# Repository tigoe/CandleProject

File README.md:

# Candle Project	

This is my candle project. We shall see how it develops.

Tom Igoe <br>
26 June 2015

## Theory of Operation

ESP8266 modules handle the network traffic, and communicate serially to the ATTiny85, which controls the WS2812s. When the candle turns on, it turns two pixels to warm fading, and a thirs to blue. Then the ESP8266 attempts to contact the server. When it succeeds, the third pixel is turned to warm fading.

The metal can of the candle forms a capacitive touch sensor. When a touch is detected, the candle flares the pixels to white, and sends a signal to the server. The server then sends the same message to all the candles, causing them all to flare white. They gradually fade back to the warm glow.

## Communication Protocol

All communications are over UDP. When a new client connects, the server sends "Hello!!!" to the client. When any candle sends a message to the server, the server echoes it to all servers that it's seen since launch.

When a candle receives a * message, it flares white. Similarly, when it receives a touch, it sends a * message.

* Programming

The ATTinys must be removed and programmed with a hardware programmer. The ESP modules can be programmed over the serial connection. The ground of the serial connection is the pin closest to the outside edge of the board. You need to press the IO0 button then the reset on the ESP8266 to put it in programming mode. The  indicator light will grow a dim red when you are in programming mode.

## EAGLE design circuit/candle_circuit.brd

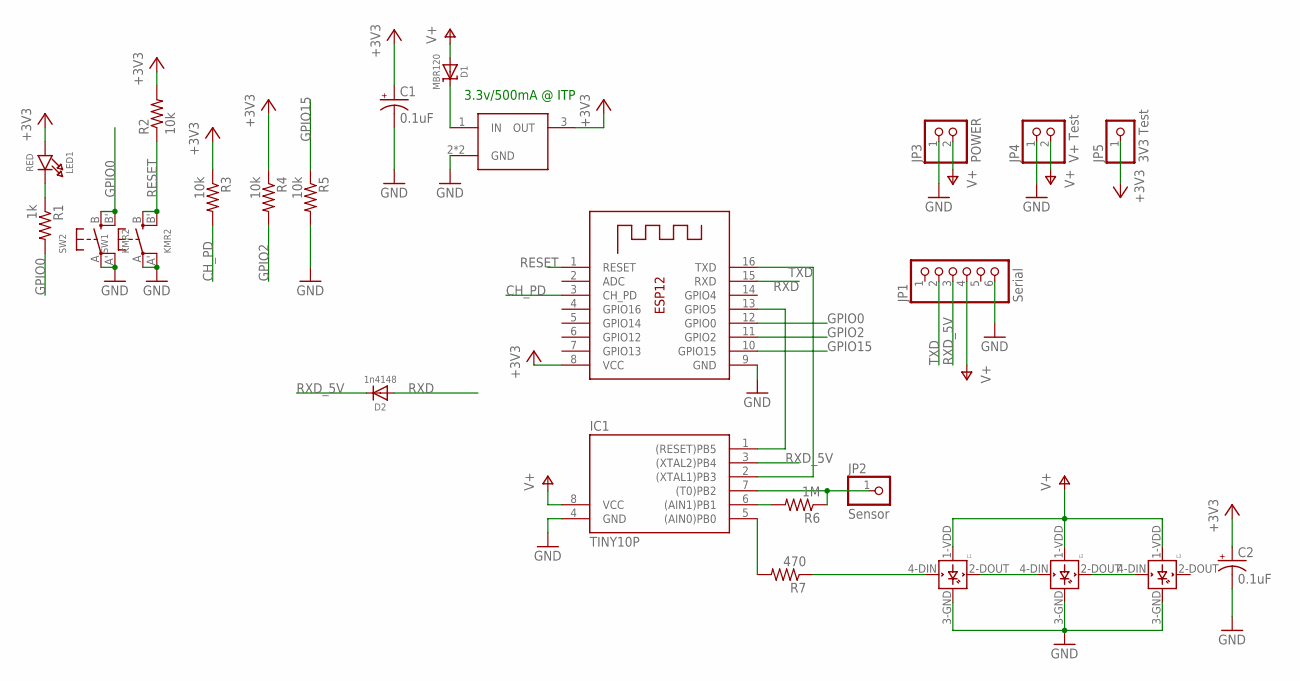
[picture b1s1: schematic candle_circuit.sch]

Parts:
C1, C2: 0.1uF; PANASONIC_C
D1: MBR120; SOD-123
D2: 1n4148; SOD-323
IC1: TINY10P; DIL08
IC2: ESP-12
JP1: Serial; 1X06_OVAL
JP2: Sensor; 1X01
JP3: POWER; 1X02_OVAL
JP4: V+ Test; 1X02_OVAL
JP5: 3V3 Test; 1X01
L1, L2, L3: WS2812B
LED1: RED; CHIPLED_0805_NOOUTLINE
R1: 1k; R0603
R2, R3, R4, R5: 10k; R0603
R6: 1M; R0603
R7: 470; R0603
SW1, SW2: KMR2; BTN_KMR2_4.6X2.8
U1: REGULATOR3.3V-UA78M33CDCYR; SOT223

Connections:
+3V3: C1.+, C2.+, IC2.8 (VCC), JP5.1, LED1.A, R2.2, R3.1, R4.1, U1.3 (OUT)
CH_PD: IC2.3 (CH_PD), R3.2
GND: C1.-, C2.-, IC1.4 (GND), IC2.9 (GND), JP1.6, JP3.1, JP4.1, L1.3-GND (GND), L2.3-GND (GND), L3.3-GND (GND), R5.2, SW1.A, SW1.A' (P1), SW2.A, SW2.A' (P1), U1.2 (GND), U1.4 (GND)
GPIO0: IC2.12 (GPIO0), R1.2, SW2.B (S), SW2.B' (S1)
GPIO2: IC2.11 (GPIO2), R4.2
GPIO15: IC2.10 (GPIO15), R5.1
unnamed: IC1.5 ((AIN0)PB0), R7.2
unnamed: L1.2-DOUT (DOUT), L2.4-DIN (DIN)
unnamed: L2.2-DOUT (DOUT), L3.4-DIN (DIN)
unnamed: IC1.1 ((RESET)PB5), IC2.13 (GPIO5)
unnamed: D1.C, U1.1 (IN)
unnamed: LED1.C, R1.1
unnamed: IC1.6 ((AIN1)PB1), R6.2
unnamed: L1.4-DIN (DIN), R7.1
RESET: IC2.1 (RESET), R2.1, SW1.B (S), SW1.B' (S1)
RXD: D2.A, IC2.15 (RXD)
RXD_5V: D2.C, IC1.3 ((XTAL2)PB4), JP1.3
SENSOR: IC1.7 ((T0)PB2), JP2.1, R6.1
TXD: IC1.2 ((XTAL1)PB3), IC2.16 (TXD), JP1.2
V+: D1.A, IC1.8 (VCC), JP1.4, JP3.2, JP4.2, L1.1-VDD (VDD), L2.1-VDD (VDD), L3.1-VDD (VDD)

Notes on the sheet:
3.3v/500mA @ ITP

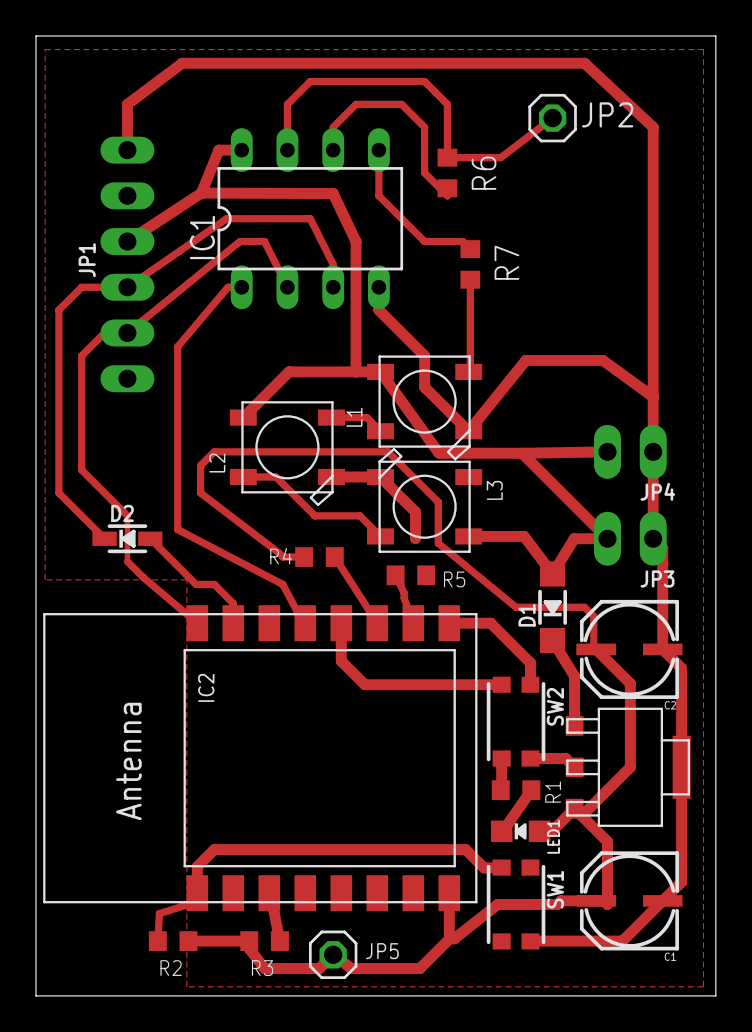
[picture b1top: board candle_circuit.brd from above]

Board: 2 copper layers, 37.8 x 53.3 mm, 25 parts (0 on the bottom side), 20 nets.

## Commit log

2015-06-27 include circuit diagrams
2015-06-27 move network settings to a header file
2015-06-27 update network client
2015-06-27 gitgnore settings for wifi client
2015-06-27 Updated candle and network client
2015-06-27 updated sensor threshold
2015-06-27 Added online/offline indicators
2015-06-28 updated candleServer
2015-06-28 Significant changes to server, added web files
2015-06-29 latest updates
2015-06-30 Added eagle files
2015-06-30 server fix
2015-06-30 updated parts, and started board layout
2015-06-30 cleanup
2015-07-01 Changes to attend code
2015-07-01 Update to client and ATTiny code
2015-07-02 Updates to circuit, client
2015-07-02 about to cut
2015-07-02 new test
2015-07-03 Circuit board updates
2015-07-03 board update
2015-07-03 Board updates
2015-07-03 changes to client and candle driver
2015-07-03 gitignore
2015-07-03 deleted Eagle backups
2015-07-03 Deleted Fritzing version
2015-07-03 Updates to board and schematic
2015-07-07 Updates to client
2015-07-10 updated twinkle threshold in candle driver
2015-07-10 client update
2015-07-10 possible fix for event emitter problem
2015-07-10 update comments
2015-07-16 Added spacer construction draeing
2015-07-16 updated PixelCandle
2015-07-16 added string controller
2015-07-17 Added assembly instructions
2015-07-18 updatedStringLight
2015-07-18 Updated colors and behavior on strings
2015-07-20 Added color setter test app
2015-07-20 stringLightTest update
2015-07-20 updated login on neoPixelString
2015-07-20 updated ESP client to send MAC address
2015-07-26 added various assembly files
2015-07-26 UDP server
2015-07-26 update to Telnet client
2015-07-26 added Wifi UDP client
2015-07-26 added UDP test client
2015-07-26 updated candle driver code
2015-07-26 updated UDP server
2015-07-26 Updaged UDP client
2015-07-26 Updated candle driver
2015-07-27 added package.json for UDP server
2015-07-27 candle firmware cleanup
2015-07-27 comments for UDPClient
2015-07-28 Updated candleServerUDP
2015-07-28 Updated ESP UDP client
2015-07-28 Added NeopixelStringUDP
2015-07-28 Updated StringLightTest
2015-07-28 Added UDPBridge.py
2015-07-29 updated UDP server and both UDP clients
2015-07-29 updates to udp server
2015-07-29 updated candleServer with web UI
2015-07-29 added webUI
2015-07-29 updated UDP server and web UI
2015-08-16 Updates to server and web client
2015-08-16 update to string lights
2015-11-16 updated BOM and assembly details
2015-11-16 Added ESPUDPCandle
    This candle can act as the wifi router for other candles.
2015-11-16 added Wifi Candle client
    Acts as both Wifi access point and UDP server
2019-10-05 update UDPAPCAndle
2019-10-07 APA102 candle added
2019-10-07 added WiFiNINA_AP, updated ESPWifiUDPClient
2019-10-07 updated candle assembly and readme.md
2020-06-06 Create Troubleshooting notes ITP40 10-10-19

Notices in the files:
parts and their libraries:
SparkFun-Capacitors: Licensing: Creative Commons ShareAlike 4.0 International - https://creativecommons.org/licenses/by-sa/4.0
microbuilder: This work is placed in the public domain, and may be freely used for commercial and non-commercial work with the following conditions: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
